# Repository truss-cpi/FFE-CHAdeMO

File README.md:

# FFE-CHAdeMO
Code and info for after-market CHAdeMO modifications to the Ford Focus Electric

The data provided has not been vetted or officially validated in any way. It is provided with no warranty and is used entirely at your own risk. 

High Voltage DC can easily maim or kill and should only be worked on by appropriately trained professionals.

You assume all responsibility if you damage anything or hurt/kill anyone using this code or information - and you agree that the creator of this repository will not be held liable in any way.

Remember: Not only will this kill you, it will hurt the whole time you're dying.

UPDATE:
A redesign of the control circuit is under way using parts that are more readily attainable and that do not require surface mount soldering. The ADM3052 is getting replaced by an MCP2561 High Speed CAN Transceiver, with SFH636 High Speed (1MBit) Optocouplers carrying the CAN0 Rx/Tx between the two isolated sections of the shield. These couplers are good for 2MHz switching frequency and the 500kbit data rate we're using should only need half that.

Validation is in progress with a "test" version of the shield code that can verify inputs/outputs, relay control and CAN transmission.

It should be noted that if the CAN1RX pin (DAC0) is not pulled up to 3.3V during validation testing, the CAN1TX pin (53) will not output test data reliably.

Also, the lowest CANBus data rate supported by the Arduino Due is 40kbit. Seen other lower values noted elsewhere but that seems to be the lowest value required by the CANBus spec and is the lowest that gave output when set on the Due.

New schematics to follow soon followed by a new board layout.

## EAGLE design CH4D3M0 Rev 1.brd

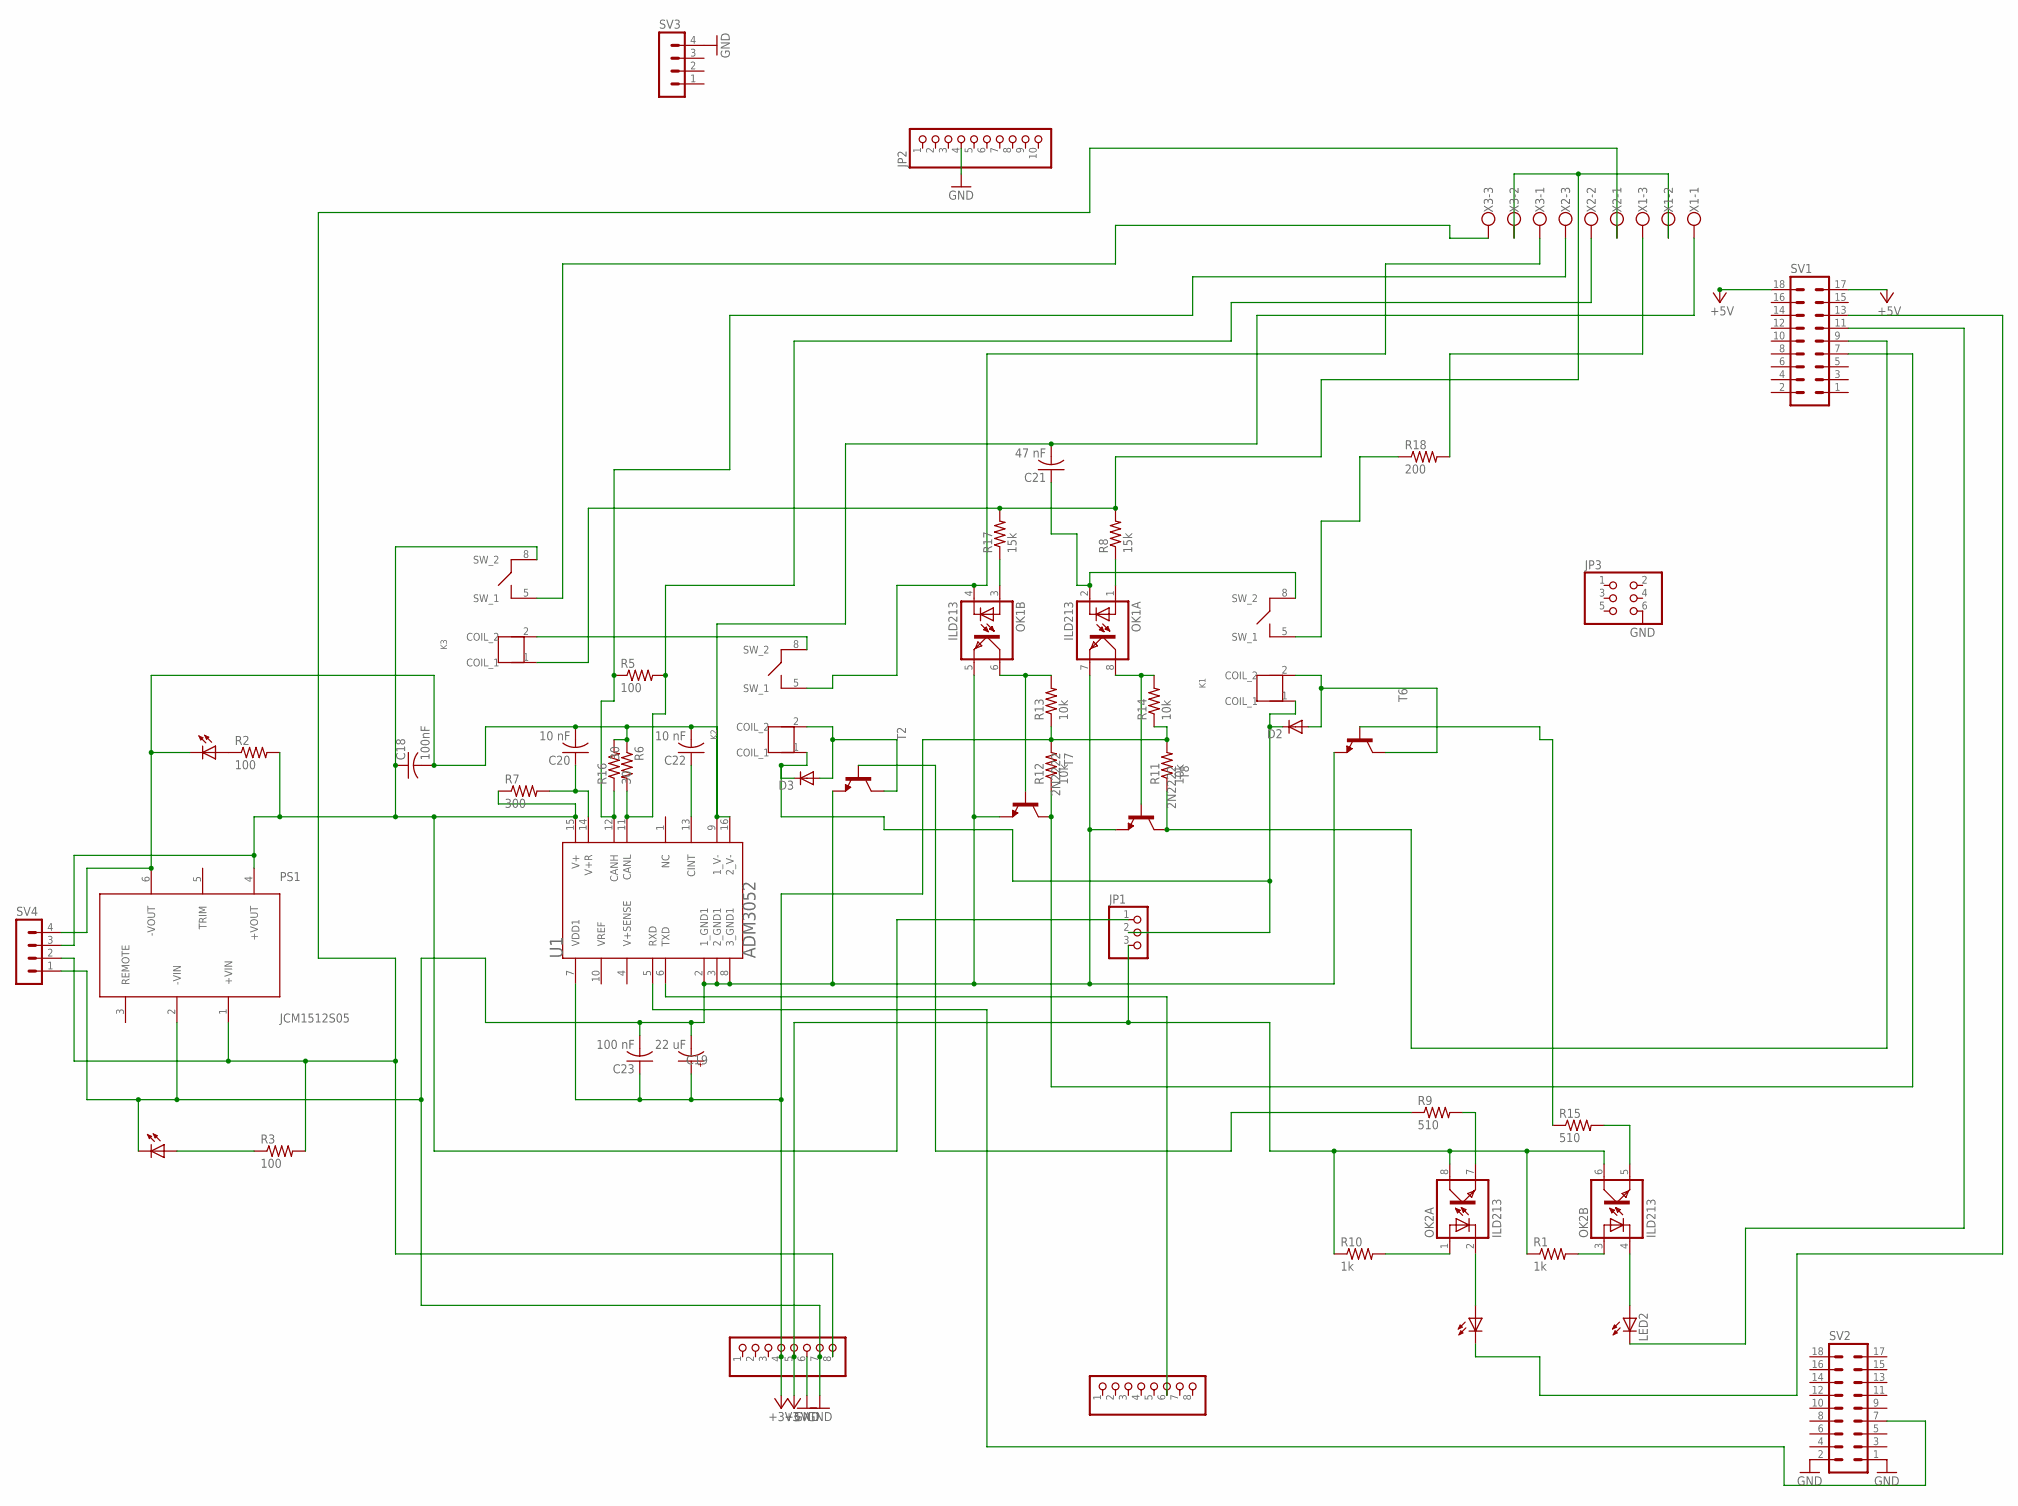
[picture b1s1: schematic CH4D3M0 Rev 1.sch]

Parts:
ADCH, ADCH2: PINHD-1X8; 1X08
C18: 100nF; C025-024X044
C19: 22 uF; E2,5RE
C20, C22: 10 nF; C025-024X044
C21: 47 nF; C025-024X044
C23: 100 nF; C025-024X044
D2, D3: DIODE-D-5; D-5
JP1: PINHD-1X3; 1X03
JP2: PINHD-1X10; 1X10
JP3: PINHD-2X3; 2X03
K1, K2, K3: G6DN-1ATHROUGH_HOLE; G6DN-1A
LED1, LED2, LED3, LED4: LED_ELD260; LED_LD260
OK1, OK2: ILD213; SOIC08
PS1: JCM1512S05; JCMXX
R1, R10: 1k; 0204/7
R2, R3, R5: 100; 0204/7
R6, R16: 30; 0204/7
R7: 300; 0204/7
R8, R17: 15k; 0204/7
R9, R15: 510; 0204/7
R11, R12, R13, R14: 10k; 0204/7
R18: 200; 0204/7
SV1, SV2: MA09-2
SV3, SV4: MA04-1
T2, T6: BC547-NPN-TO92-CBE; TO92-CBE
T7, T8: 2N2222; TO92-EBC-OVAL
U1: ANALOG_DEVICES_INC_ADM3052ANALOG_DEVICES_INC_ADM3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; ANALOG_DEVICES_INC_ADM3052_0
X1, X2, X3: W237-103

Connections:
+3V3: ADCH2.4, C19.+, C23.1, R11.2, R12.2, R13.1, R14.1, U1.7 (VDD1)
+5V: ADCH2.5, JP1.3, OK2.6 (COL), OK2.8 (COL), R1.1, R10.1, SV1.17, SV1.18
GND: ADCH2.6, ADCH2.7, C19.-, C23.2, JP2.4, JP3.6, LED4.K (C), OK1.5 (EMIT), OK1.7 (EMIT), PS1.2 (-VIN), SV2.1, SV2.2, SV3.4, SV4.1, T2.E, T6.E, T7.E, T8.E, U1.2 (1_GND1), U1.3 (2_GND1), U1.8 (3_GND1)
unnamed: D2.C, D3.C, JP1.2, K1.1 (COIL_1), K2.1 (COIL_1)
unnamed: C18.1, JP1.1, K3.8 (SW_2), PS1.4 (+VOUT), R2.2, R7.1, SV4.3, U1.15 (V+)
unnamed: C20.1, R7.2, U1.14 (V+R)
unnamed: C22.1, U1.13 (CINT)
unnamed: K3.5 (SW_1), X3.3
unnamed: R18.2, X1.3
unnamed: C18.2, C20.2, C21.2, C22.2, LED3.K (C), PS1.6 (-VOUT), R6.1, R16.2, SV4.4, U1.9 (1_V-), U1.16 (2_V-), X1.1
unnamed: R5.2, R6.2, U1.11 (CANL), X2.2
unnamed: C21.1, K1.8 (SW_2), OK1.2 (C)
unnamed: K1.5 (SW_1), R18.1
unnamed 13: K3.1 (COIL_1), R8.2, R17.2, X1.2, X3.2; also elsewhere on the board
unnamed: OK1.1 (A), R8.1
unnamed: OK1.3 (A), R17.1
unnamed: ADCH2.8, PS1.1 (+VIN), R3.2, SV4.2, X2.1
unnamed 17: K2.8 (SW_2), K3.2 (COIL_2); also elsewhere on the board
unnamed: K2.5 (SW_1), OK1.4 (C), X3.1
unnamed: OK1.6 (COL), R13.2, T7.B
unnamed: OK1.8 (COL), R14.2, T8.B
unnamed: R12.1, SV1.7, T7.C
unnamed: ADCH.6, U1.6 (TXD)
unnamed: R11.1, SV1.9, T8.C
unnamed: SV2.7, U1.5 (RXD)
unnamed: D2.A, K1.2 (COIL_2), T6.C
unnamed: D3.A, K2.2 (COIL_2), T2.C
unnamed: OK2.7 (EMIT), R9.2
unnamed: LED1.A, OK2.2 (C)
unnamed: OK2.1 (A), R10.2
unnamed: OK2.3 (A), R1.2
unnamed: R9.1, T2.B
unnamed: LED1.K (C), SV1.13
unnamed: R15.1, T6.B
unnamed: OK2.5 (EMIT), R15.2
unnamed: LED2.A, OK2.4 (C)
unnamed: LED2.K (C), SV1.11
unnamed: R5.1, R16.1, U1.12 (CANH), X2.3
unnamed: LED3.A, R2.1
unnamed: LED4.A, R3.1

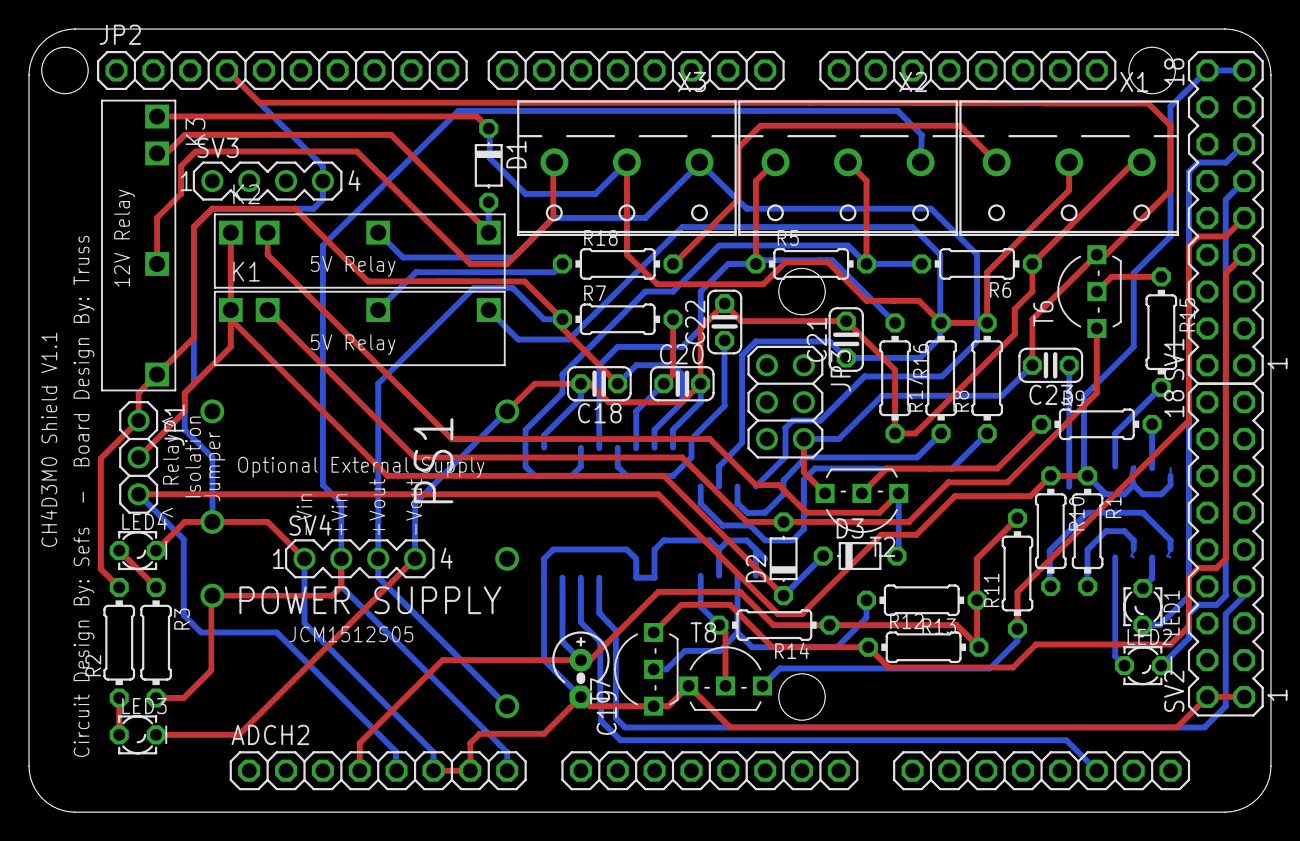
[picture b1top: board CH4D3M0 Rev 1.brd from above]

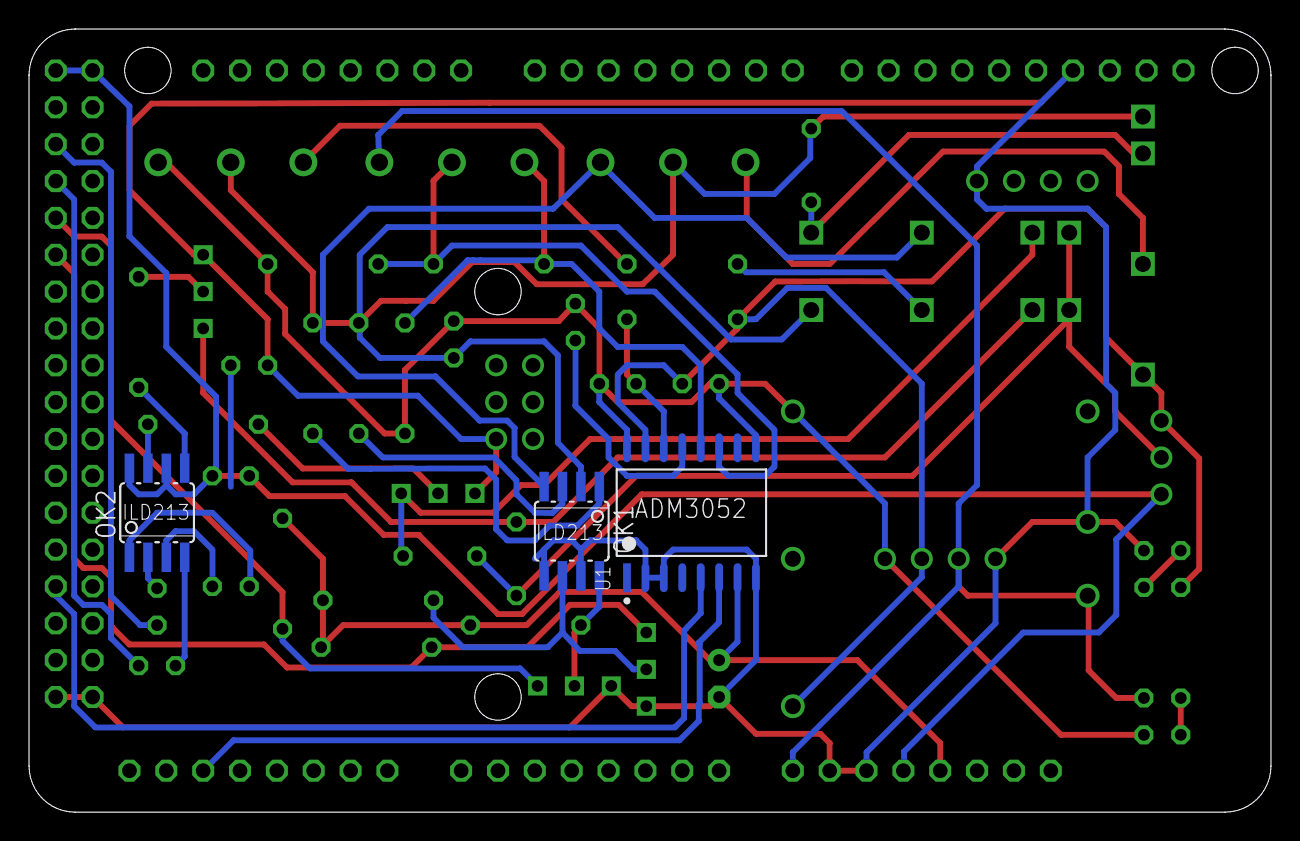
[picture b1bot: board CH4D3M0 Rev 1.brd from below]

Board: 2 copper layers, 85.6 x 54.0 mm, 56 parts (3 on the bottom side), 40 nets.

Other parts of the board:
ADCL: 1X08
COMMUNICATION: 1X08
D1: D-5
PWML: 1X08

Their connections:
unnamed 13: D1.C; also elsewhere on the board
unnamed 17: D1.A; also elsewhere on the board

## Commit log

2021-12-14 Update README.md
    Initial readme framework - I will not be held liable
2021-12-14 Create LICENSE
2021-12-14 Add files via upload
    Vehicle-side Arduino code for managing CHAdeMO operation. Additional code included for serial-based monitoring/display app.
2022-01-11 Add files via upload
    This board and schematic should be examined before use - I am not a board designer and almost certainly run afoul of best practices.
2022-01-11 Add files via upload
    Diagram of the original circuit
2022-01-18 Create Schematic Overview Details
2022-01-18 Create Vehicle CHAdeMO Parts List
2022-01-19 Create Vehicle CHAdeMO Shield Parts
2022-03-24 Rename arduino.c to Onboard_CHAdeMO/arduino.c
2022-03-24 Rename External_Charger/sodbm_controller_A.ino to External_Charger/Module_Control/sodbm_controller.ino
2022-05-01 Rename CH4D3M0 Rev 1.brd to CH4D3M0 Rev 1.1.brd
    Updated schematic and board layout with snubber diode for 12V relay
2022-05-01 Rename CH4D3M0 Rev 1.sch to CH4D3M0 Rev 1.1.sch
    Updated schematic with snubber diode for 12V relay and corrected capacitor value(s)
2022-05-01 Update Vehicle CHAdeMO Shield Parts
    Completed parts list.
2022-05-01 Update Vehicle CHAdeMO Shield Parts
2022-06-11 Update README.md
    Flaws in original board design have been found and are being reworked/tested
